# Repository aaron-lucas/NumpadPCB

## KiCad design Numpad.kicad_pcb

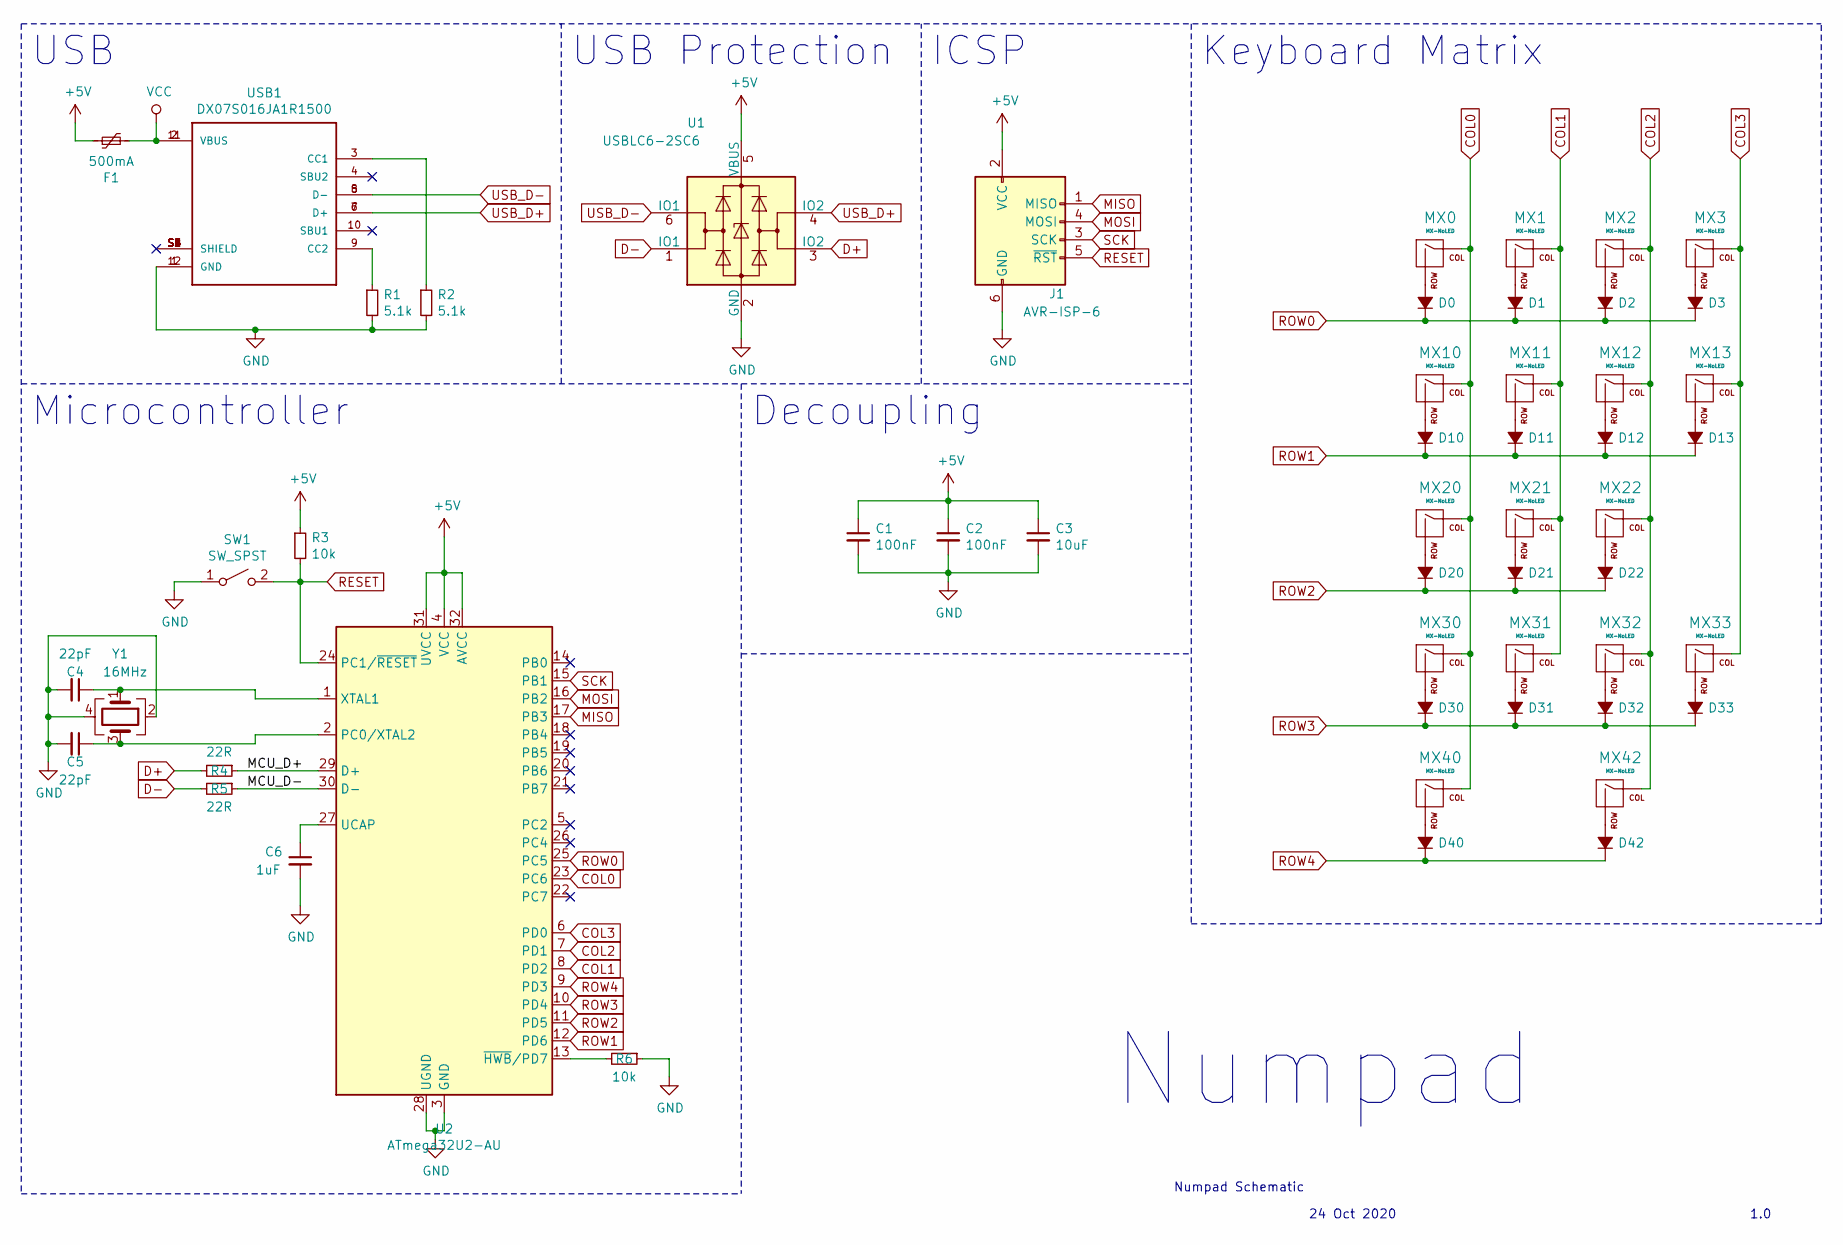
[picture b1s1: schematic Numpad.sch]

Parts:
C1, C2: 100nF; C_0603_1608Metric; LCSC C1525
C3: 10uF; C_0603_1608Metric; LCSC C19702
C4, C5: 22pF; C_0603_1608Metric; LCSC C1555
C6: 1uF; C_0603_1608Metric; LCSC C52923
D0, D1, D2, D3, D10, D11, D12, D13, D20, D21, D22, D30, D31, D32, D33, D40, D42: D_Small_ALT; D_SOD-123; LCSC C183407
F1: 500mA; Fuse_0603_1608Metric; LCSC C261937
J1: AVR-ISP-6; PinHeader_2x03_P2.54mm_Vertical
MX0, MX1, MX2, MX3, MX10, MX11, MX12, MX20, MX21, MX22, MX30, MX31, MX32, MX42: MX-NoLED; MXOnly-1U-NoLED
MX13, MX33, MX40: MX-NoLED; MXOnly-2U-ReversedStabilizers-NoLED
R1, R2: 5.1k; R_0603_1608Metric; LCSC C25905
R3, R6: 10k; R_0603_1608Metric; LCSC C25744
R4, R5: 22R; R_0603_1608Metric; LCSC C25092
SW1: SW_SPST; TACTILE_SWITCH_SPST_SMD_5.2MM
U1: USBLC6-2SC6; SOT-23-6; LCSC C7519
U2: ATmega32U2-AU; TQFP-32_7x7mm_P0.8mm
USB1: DX07S016JA1R1500; JAE_DX07S016JA1R1500
Y1: 16MHz; Crystal_SMD_3225-4Pin_3.2x2.5mm; LCSC C13738

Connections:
+5V: C1.1, C2.1, C3.1, F1.1, J1.2 (VCC), R3.1, U1.5 (VBUS), U2.4 (VCC), U2.31 (UVCC), U2.32 (AVCC); also elsewhere on the board
/MCU_D+: R4.1, U2.29 (D+)
/MCU_D-: R5.1, U2.30 (D-)
COL0: MX0.1 (COL), MX10.1 (COL), MX20.1 (COL), MX30.1 (COL), MX40.1 (COL), U2.23 (PC6)
COL1: MX1.1 (COL), MX11.1 (COL), MX21.1 (COL), MX31.1 (COL), U2.8 (PD2)
COL2: MX2.1 (COL), MX12.1 (COL), MX22.1 (COL), MX32.1 (COL), MX42.1 (COL), U2.7 (PD1)
COL3: MX3.1 (COL), MX13.1 (COL), MX33.1 (COL), U2.6 (PD0)
D+: R4.2, U1.3 (IO2)
D-: R5.2, U1.1 (IO1)
GND: C1.2, C2.2, C3.2, C4.2, C5.2, C6.2, J1.6 (GND), R1.2, R2.2, R6.1, SW1.1 (A), U1.2 (GND), U2.3 (GND), U2.28 (UGND), USB1.1 (GND), USB1.12 (GND), Y1.2, Y1.4; also elsewhere on the board
MISO: J1.1 (MISO), U2.17 (PB3); also elsewhere on the board
MOSI: J1.4 (MOSI), U2.16 (PB2); also elsewhere on the board
unnamed: C4.1, U2.1 (XTAL1), Y1.1
unnamed: C5.1, U2.2 (PC0/XTAL2), Y1.3
unnamed: C6.1, U2.27 (UCAP)
unnamed: D0.2 (A), MX0.2 (ROW)
unnamed: D1.2 (A), MX1.2 (ROW)
unnamed: D2.2 (A), MX2.2 (ROW)
unnamed: D3.2 (A), MX3.2 (ROW)
unnamed: D10.2 (A), MX10.2 (ROW)
unnamed: D11.2 (A), MX11.2 (ROW)
unnamed: D12.2 (A), MX12.2 (ROW)
unnamed: D13.2 (A), MX13.2 (ROW)
unnamed: D20.2 (A), MX20.2 (ROW)
unnamed: D21.2 (A), MX21.2 (ROW)
unnamed: D22.2 (A), MX22.2 (ROW)
unnamed: D30.2 (A), MX30.2 (ROW)
unnamed: D31.2 (A), MX31.2 (ROW)
unnamed: D32.2 (A), MX32.2 (ROW)
unnamed: D33.2 (A), MX33.2 (ROW)
unnamed: D40.2 (A), MX40.2 (ROW)
unnamed: D42.2 (A), MX42.2 (ROW)
unnamed: R1.1, USB1.9 (CC2)
unnamed: R2.1, USB1.3 (CC1)
unnamed: R6.2, U2.13 (~HWB~/PD7)
unnamed: USB1.S1 (SHIELD), USB1.S2 (SHIELD), USB1.S3 (SHIELD), USB1.S4 (SHIELD), USB1.S5 (SHIELD), USB1.S6 (SHIELD)
RESET: J1.5 (~RST), R3.2, SW1.2 (B), U2.24 (PC1/~RESET); also elsewhere on the board
ROW0: D0.1 (K), D1.1 (K), D2.1 (K), D3.1 (K), U2.25 (PC5)
ROW1: D10.1 (K), D11.1 (K), D12.1 (K), D13.1 (K), U2.12 (PD6)
ROW2: D20.1 (K), D21.1 (K), D22.1 (K), U2.11 (PD5)
ROW3: D30.1 (K), D31.1 (K), D32.1 (K), D33.1 (K), U2.10 (PD4)
ROW4: D40.1 (K), D42.1 (K), U2.9 (PD3)
SCK: J1.3 (SCK), U2.15 (PB1); also elsewhere on the board
USB_D+: U1.4 (IO2), USB1.6 (D+), USB1.7 (D+)
USB_D-: U1.6 (IO1), USB1.5 (D-), USB1.8 (D-)
VCC: F1.2, USB1.2 (VBUS), USB1.11 (VBUS)

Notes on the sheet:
Numpad
Numpad Schematic
24 Oct 2020
1.0
Microcontroller
USB
USB Protection
ICSP
Decoupling
Keyboard Matrix

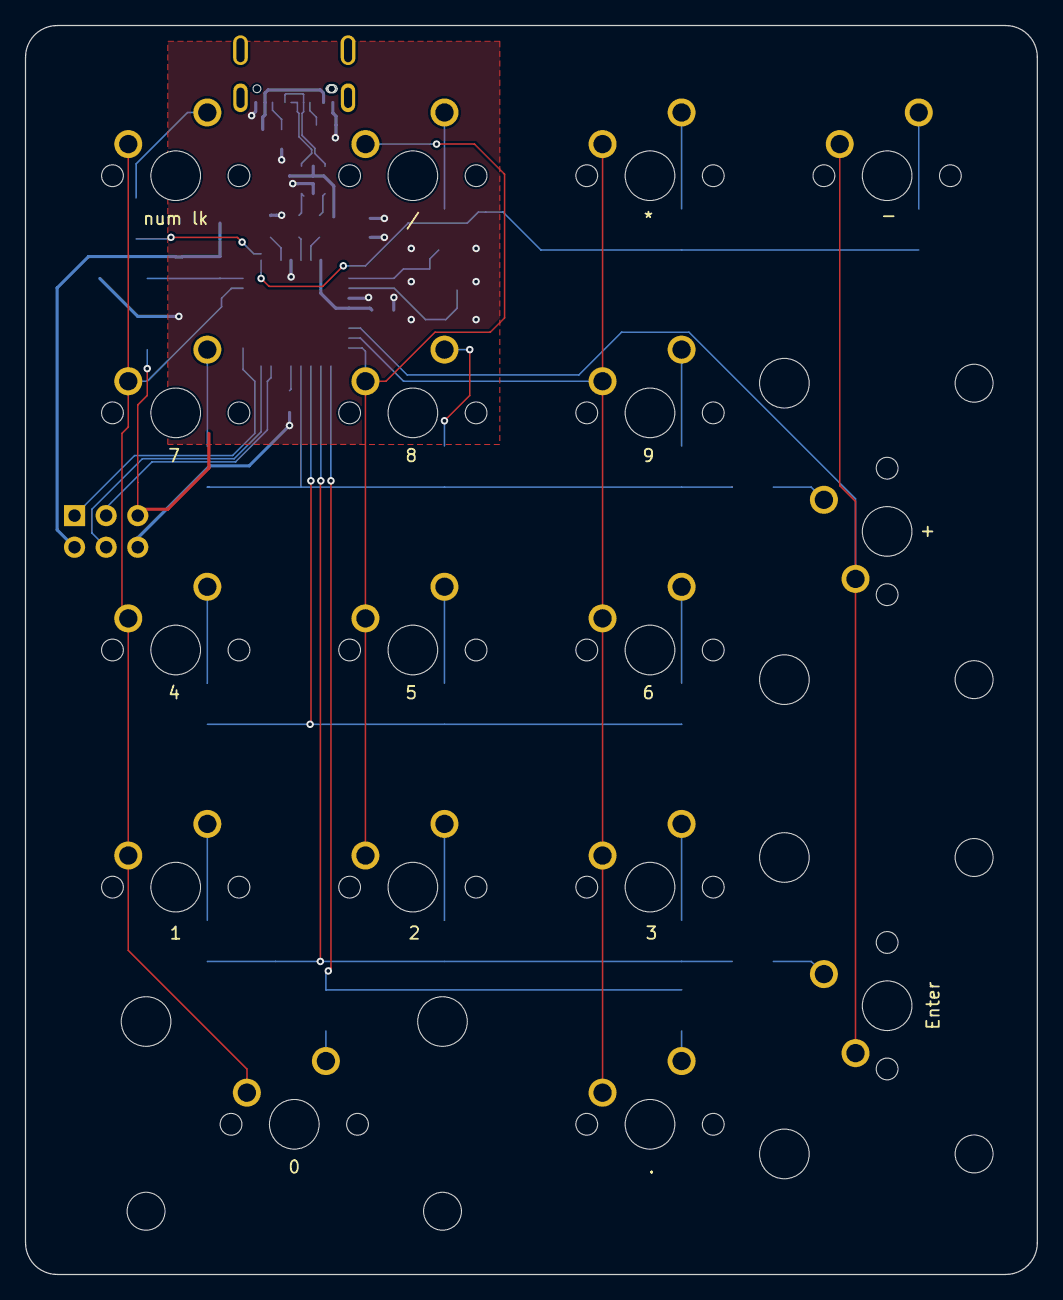
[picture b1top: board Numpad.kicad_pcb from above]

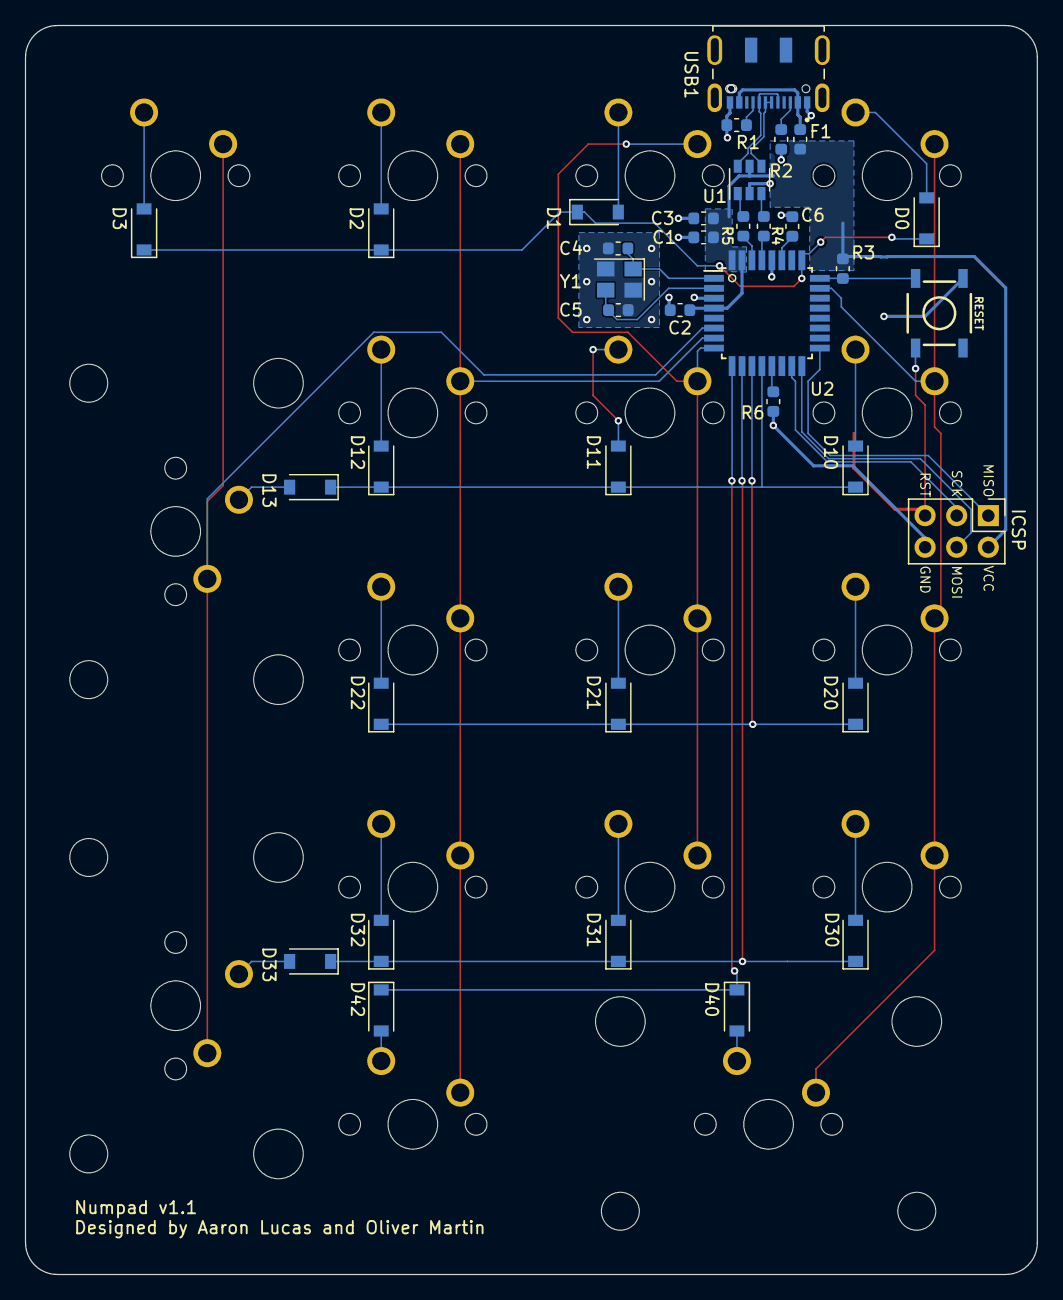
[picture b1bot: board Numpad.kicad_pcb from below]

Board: 2 copper layers, 81.3 x 100.3 mm, 53 parts (36 on the bottom side), 46 nets.

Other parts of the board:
ICSP: AVR-ISP-6; PinHeader_2x03_P2.54mm_Vertical
RESET: SW_SPST; TACTILE_SWITCH_SPST_SMD_5.2MM

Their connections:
+5V: ICSP.2; also elsewhere on the board
GND: ICSP.6, RESET.1; also elsewhere on the board
MISO: ICSP.1; also elsewhere on the board
MOSI: ICSP.4; also elsewhere on the board
RESET: ICSP.5, RESET.2; also elsewhere on the board
SCK: ICSP.3; also elsewhere on the board

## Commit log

2020-08-26 Project setup
2020-08-26 Add submodules
2020-08-26 Add other submodule
2020-08-26 Add libraries
2020-08-26 Complete Schematic
2020-08-26 Save progress
2020-08-28 Adjust schematic layout
2020-10-22 Commit all files before starting from scratch
2020-10-22 Restart project
2020-10-24 Complete PCB v1
2021-01-16 Fix issues with reset button and bootloader mode
